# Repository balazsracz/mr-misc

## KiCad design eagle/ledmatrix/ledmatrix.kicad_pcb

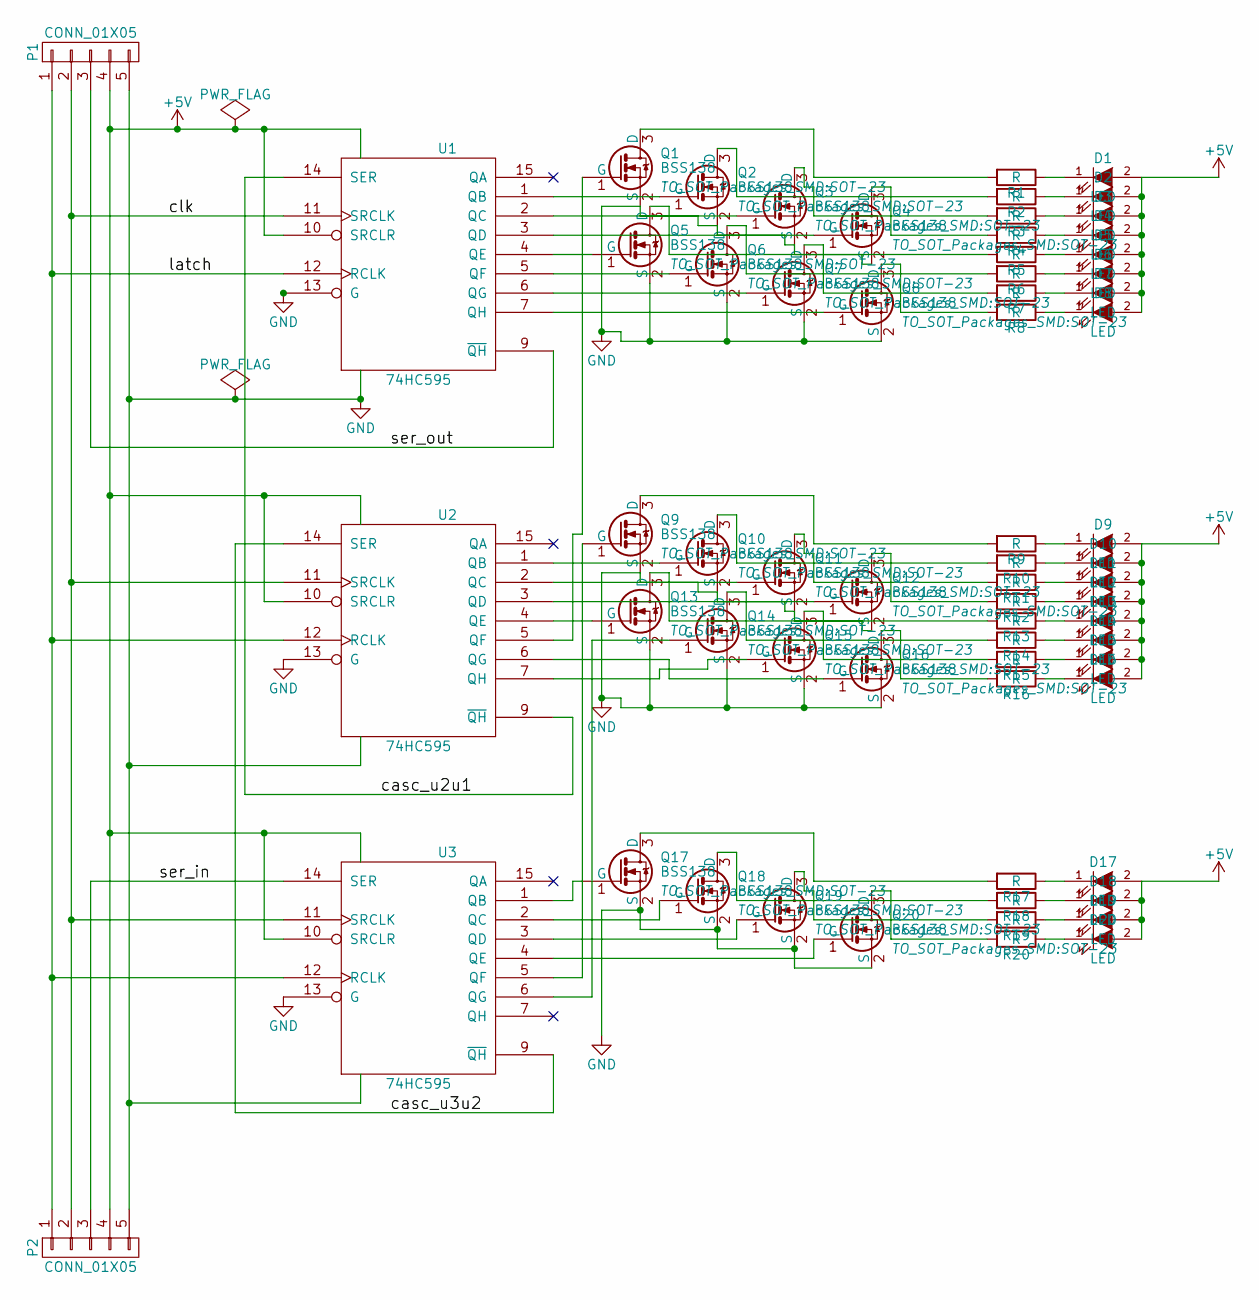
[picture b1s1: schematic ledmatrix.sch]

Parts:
D1, D2, D3, D4, D5, D6, D7, D8, D9, D10, D11, D12, D13, D14, D15, D16, D17, D18, D19, D20: LED; LED_PLCC_2835_Handsoldering
P1, P2: CONN_01X05; Pin_Header_Straight_1x05
Q1, Q2, Q3, Q4, Q5, Q6, Q7, Q8, Q9, Q10, Q11, Q12, Q13, Q14, Q15, Q16, Q17, Q18, Q19, Q20: BSS138; SOT-23
R1, R2, R3, R4, R5, R6, R7, R8, R9, R10, R11, R12, R13, R14, R15, R16, R17, R18, R19, R20: R; R_0805_HandSoldering
U1, U2, U3: 74HC595; SOIC-16_3.9x9.9mm_Pitch1.27mm

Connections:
+5V: D1.2 (A), D2.2 (A), D3.2 (A), D4.2 (A), D5.2 (A), D6.2 (A), D7.2 (A), D8.2 (A), D9.2 (A), D10.2 (A), D11.2 (A), D12.2 (A), D13.2 (A), D14.2 (A), D15.2 (A), D16.2 (A), D17.2 (A), D18.2 (A), D19.2 (A), D20.2 (A), P1.4, P2.4, U1.10 (SRCLR), U1.16 (VCC), U2.10 (SRCLR), U2.16 (VCC), U3.10 (SRCLR), U3.16 (VCC)
/casc_u2u1: U1.14 (SER), U2.9 (~QH)
/casc_u3u2: U2.14 (SER), U3.9 (~QH)
/clk: P1.2, P2.2, U1.11 (SRCLK), U2.11 (SRCLK), U3.11 (SRCLK)
/latch: P1.1, P2.1, U1.12 (RCLK), U2.12 (RCLK), U3.12 (RCLK)
/ser_in: P2.3, U3.14 (SER)
/ser_out: P1.3, U1.9 (~QH)
GND: P1.5, P2.5, Q1.2 (S), Q2.2 (S), Q3.2 (S), Q4.2 (S), Q5.2 (S), Q6.2 (S), Q7.2 (S), Q8.2 (S), Q9.2 (S), Q10.2 (S), Q11.2 (S), Q12.2 (S), Q13.2 (S), Q14.2 (S), Q15.2 (S), Q16.2 (S), Q17.2 (S), Q18.2 (S), Q19.2 (S), Q20.2 (S), U1.8 (GND), U1.13 (G), U2.8 (GND), U2.13 (G), U3.8 (GND), U3.13 (G)
unnamed: D1.1 (K), R1.1
unnamed: D2.1 (K), R2.1
unnamed: D3.1 (K), R3.1
unnamed: D4.1 (K), R4.1
unnamed: D5.1 (K), R5.1
unnamed: D6.1 (K), R6.1
unnamed: D7.1 (K), R7.1
unnamed: D8.1 (K), R8.1
unnamed: D9.1 (K), R9.1
unnamed: D10.1 (K), R10.1
unnamed: D11.1 (K), R11.1
unnamed: D12.1 (K), R12.1
unnamed: D13.1 (K), R13.1
unnamed: D14.1 (K), R14.1
unnamed: D15.1 (K), R15.1
unnamed: D16.1 (K), R16.1
unnamed: D17.1 (K), R17.1
unnamed: D18.1 (K), R18.1
unnamed: D19.1 (K), R19.1
unnamed: D20.1 (K), R20.1
unnamed: Q1.1 (G), U2.5 (QF)
unnamed: Q1.3 (D), R1.2
unnamed: Q2.1 (G), U1.1 (QB)
unnamed: Q2.3 (D), R2.2
unnamed: Q3.1 (G), U1.2 (QC)
unnamed: Q3.3 (D), R3.2
unnamed: Q4.1 (G), U1.3 (QD)
unnamed: Q4.3 (D), R4.2
unnamed: Q5.1 (G), U1.4 (QE)
unnamed: Q5.3 (D), R5.2
unnamed: Q6.1 (G), U1.5 (QF)
unnamed: Q6.3 (D), R6.2
unnamed: Q7.1 (G), U1.6 (QG)
unnamed: Q7.3 (D), R7.2
unnamed: Q8.1 (G), U1.7 (QH)
unnamed: Q8.3 (D), R8.2
unnamed: Q9.1 (G), U3.5 (QF)
unnamed: Q9.3 (D), R9.2
unnamed: Q10.1 (G), U2.1 (QB)
unnamed: Q10.3 (D), R10.2
unnamed: Q11.1 (G), U2.2 (QC)
unnamed: Q11.3 (D), R11.2
unnamed: Q12.1 (G), U2.3 (QD)
unnamed: Q12.3 (D), R12.2
unnamed: Q13.1 (G), U2.4 (QE)
unnamed: Q13.3 (D), R13.2
unnamed: Q14.1 (G), U3.6 (QG)
unnamed: Q14.3 (D), R14.2
unnamed: Q15.1 (G), U2.7 (QH)
unnamed: Q15.3 (D), R15.2
unnamed: Q16.1 (G), U2.6 (QG)
unnamed: Q16.3 (D), R16.2
unnamed: Q17.1 (G), U3.1 (QB)
unnamed: Q17.3 (D), R17.2
unnamed: Q18.1 (G), U3.2 (QC)
unnamed: Q18.3 (D), R18.2
unnamed: Q19.1 (G), U3.3 (QD)
unnamed: Q19.3 (D), R19.2
unnamed: Q20.1 (G), U3.4 (QE)
unnamed: Q20.3 (D), R20.2

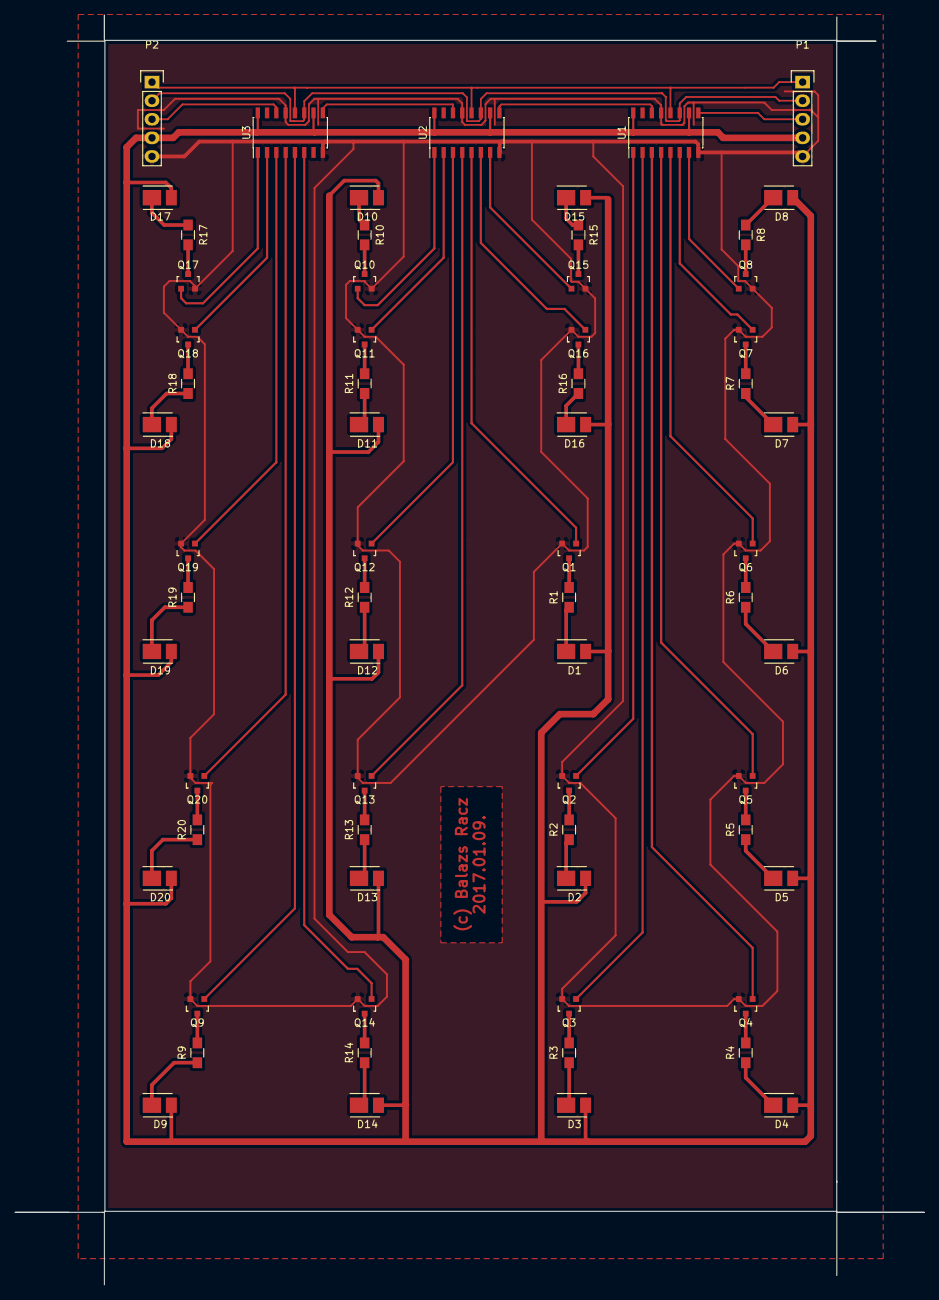
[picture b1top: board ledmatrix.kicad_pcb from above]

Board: 2 copper layers, 100.0 x 160.0 mm, 65 parts (0 on the bottom side), 68 nets.

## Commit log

2011-10-30 add initial list of stuff
2011-10-30 Baseline boxing command
2011-10-30 Add resistor definition command.
2011-10-30 check in CSV list
2011-11-05 finished labels tex code
2013-08-10 Workshop list generation code updates.
2013-08-10 Original source and binaries by D Nadler.
2013-08-10 Adds XC32 headers that are needed for the peripherial definitions.
2013-08-10 Changes needed to make the cpp demo compile.
2013-08-10 Removes generated files.
2013-08-10 Allows make dep to run without an exisitng depend file.
2013-08-12 Fixes compilation problems.
2013-08-12 Adpts nadler's code to PIC32MX795 on my board.
2013-08-12 Adds bootloader code with changes needed to make it compile.
2013-08-12 Adds missing file for the 795.
2013-08-12 Switches bootloader to 80MHz. Updates USB bootloader to not require interrupt flag table, which is huge. Renamed to bootloader.{elf,hex} Removes the CS3 startup code which is huge. Supplies custom st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
2013-08-12 Moves the bootloader into the bootloader area. Updates the app start pointers.
2013-08-12 Working bootloader.
2014-06-06 Updates the fuses to match the duinomite mega better. Enables block switching.
2014-06-06 Fixes compilation errors.
2014-06-06 changes the include guard to avoid clashes with openmrn.
2014-06-06 updates bootloader fuses.
2015-03-16 Adds base versions of the mixxx controller scripts.
2015-03-16 Removes the headphone volume control. Adds script bindings to the fwd and back buttons.
2015-03-16 starts adding onfwd onback javascript functions.
2015-03-16 Adds handling for onFwd.
2015-03-16 removes key off bindings from the onfwd onback commands.
2015-03-16 Fixes bug in onFwd that caused it to trigger on key up as well.
2015-03-16 Adds onBack implementation.
2015-03-16 Fixes broken script-binding.
2015-03-16 Adds a couple of buttons as soft buttons.
2015-03-16 Implements beats translation on soft button 4.
2015-04-19 moves an onsoftbutton defn.
2015-04-19 Adds the ability to catch wheel turn (not jog) operations in javascript.
2015-05-14 adds scratching support when the deck is not playing.
2015-10-25 'We use math' tex logo.
2015-10-25 adds gitignore for parts.
2015-10-25 adds gitignore.
2015-10-25 trainlib historical commit 2014-10-31
2015-10-25 trainlib historical commit 2014-10-31-2
2015-10-25 trainlib historical commit 2014-10-31-3
2015-10-25 trainlib historical commit 2014-10-31-4
2015-10-25 trainlib historical commit 2014-11-01-1
2015-10-25 trainlib historical commit 2014-11-01-2
2015-10-25 trainlib historical commit 2014-11-01-3
2015-10-25 trainlib historical commit 2015-07-25-1
2015-10-25 trainlib historical commit 2015-07-25-3
2015-10-25 trainlib historical commit 2015-07-27-1
2015-10-25 trainlib historical commit 2015-07-27-2
2015-10-25 trainlib historical commit 2015-08-31-1
2015-10-25 trainlib historical commit 2015-08-31-2
2015-10-25 trainlib historical commit 2015-08-31-3
2015-10-25 trainlib historical commit 2015-08-31-4
2015-10-25 trainlib current
2015-10-26 adds/updates rj45 jacks. adds a 0R bridge.
2015-11-27 smd reflow oven testing pattern
2015-11-27 Adds basic makefile and blink binary
2015-11-27 Adds qr code files.
2015-11-27 checks in bootloader source
2015-11-29 Adds eagle library file used by the project.
2015-12-01 adds a test of the led hardware during the bootup of the bootloader.
2015-12-01 cleanup library
2015-12-02 original bootloader offset
2015-12-02 updates codeoffset.
2015-12-02 removes outpout file
2015-12-02 ignores hex files
2015-12-02 Adds usb driver source to firmware library.
2015-12-02 adds usb options to makefile
2015-12-02 rendered schematics
2015-12-02 older version
2015-12-02 adds gitignore
2015-12-02 updates yellow on rgb
2015-12-02 cleanup blink code
2015-12-02 Adds all the steps for the firmware training.
2015-12-03 Adds binaries for flashing usb-hid bootloaders.
2015-12-03 adds mac specific makefile
2015-12-03 create bin dir
2015-12-03 actually use the flash variable
2015-12-08 Adds production firmware.
2016-05-15 Adds a test application to debug the USB-CDC device driver.
2016-05-15 Adds new device DMG6601LVT.
2016-05-15 Adds esp12-huzzah breakout board.
2016-05-15 Adds pololu voltage regulator.
2016-05-15 Finishes deadrail schematics (en gross).
2016-05-17 Adds esp12-huzzah board definition.
2016-05-17 autorouter definitions for etching.
2016-05-17 Adds all intermediate and the final schematic and board layout for the huzzah baseboard for esp-12 train decoder.
2016-06-04 Adds a bunch of parts to the lib that are used in the deadrail controller.
2016-06-04 Checks in the adafruit eagle library downloaded from their webpage.
2016-06-04 Adds first versions of the schematics for the native deadrail decoder implementation.
2016-06-05 Adds through-hole version of esp-12. Adds rectifier bridge in sot format. Adds analog mux. Adds pinheaders for hand soldering.
2016-06-05 Fixes unloadable schematics
2016-06-05 Adds all intermediate and the final rendering of the design.
2016-06-06 Adds the esp-12 in the original form from the adafruit library and makes the rounding outline smaller.
2016-06-06 Adds variants with polygon and a bunch of ground vias.
2016-06-06 Adds gerber output.
2016-06-23 submitted file.
2016-07-26 Check in compiled version of the bootloader (with full optimization so it fits in 4K).
2016-07-26 Adds dependency list.
2016-07-27 Adds a firmware that can be used to test the solder job.
2016-07-28 Stop sending zeros to the hostfrom the usb-serial device. It makes various host program confused.
2016-07-28 Change the USB-reported product name so that we can recognize these devices from software.
2016-07-28 Adds trim dependency.
2016-07-28 Adds data logger application that writes to google sheets.
2016-07-28 Actually call init().
2016-09-07 update DRU
2016-09-07 Check in ledmatrix rules.
2016-09-09 continue work on the ledmatrix schematic and board.
2016-09-09 Adds outlines.
2016-09-09 adds brokenusb test
2016-09-09 layout components.
2016-09-09 more routing -- latch, clock proposal 1
2016-09-09 all routed
2016-09-09 adds ground fill.
2016-09-09 regenrates fill. Adds rendered board.
2017-05-06 Adds drawing of the laser-cutted bridge.
2017-05-06 Adds new versions of the bridge design.
2017-05-07 New design with small fixes of the bridge
2018-04-01 Checks in missing files.
2018-04-01 Adds nucleo 64 library element.
2018-04-01 Start of the io board based on the nucleo base.
2018-04-05 Adds AP1509 and a through hole inductor.
2018-04-05 Adds version of the nucleo board with inputs, the switching PS and part of the tortoise driver.
2018-04-09 Ignores backup files by eagle.
2018-04-09 Adds seed DRU file
2018-04-09 Adds round solder jumpers; solder jumpers that are default-closed Updates DIL-8 package to have standard footprint Adds package outline to 0.1" terminal block Adds DIL18 footprint with small solder t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
2018-04-09 More work on the nucleo io board.
2018-04-14 more versions of the io board.
2018-04-15 Adds better (polygon based) round solder bridge. Moves CAN transceiver to create a small-hole DIL8 package version.
2018-04-15 Finishes routing the io board. Adds four more servo outputs.
2018-04-19 Latest versions.
2018-04-22 updates some components.
2018-04-22 Adds more iterations of the io board.
2018-05-06 Moves layer designations for the power notice component.
2018-05-06 Adds a package for denoting revision.
2018-05-06 Removes the ground polygon inside the cutaway wire of the SJ-C.
2018-05-06 Rev A final version.
2018-05-06 Moves a couple of parts to the custom library to allow renaming prefix to U instead of IC.
2018-05-06 Progress towards rev B.
2018-05-06 Adds missing prefixes.
2018-05-08 Modifies the DC jack part to not have overlapping mills and drill.
2018-05-08 New revisions to fix comments from the review process.
2018-05-12 More versions of the board design.
2018-05-12 DCjack: removes overlapping wires on the via layer that cause conflict.
2018-05-21 Adds DPDT switch adds micro-USB receptacle adds larger pinheaders adds a CC3220SF launchpad HAT footprint.
2018-05-21 Adds programming adapter board.
2018-05-21 adds individual gerber files of the jtag adapter.
2018-05-21 Adds RJ45 adaptor board.
2018-05-23 Adds deduplicator python code.
2018-05-23 Adds copyright notice
2018-05-26 Adds first covering algorithm.
2018-05-26 Adds code to apply rules specifically to filter files with lots of duplicates.
2018-06-11 Fixes launchpad jtag-HAT footprint. Fixes bounding box on siklscreen for the 0.05" jtag header.
2018-06-11 Fixes prototype problems.
2018-07-07 Imports loconet library from arduino library manager.
2018-07-07 Adds empty shell for openmrn library.
2018-07-08 moves library to src directory for 1.5. format.
2018-07-08 switches library to .a linkage.
2018-07-08 Adds symlinks to the openmrn implementation code.
2018-07-08 Adds support for Serial ports via gridconnect hub.
2018-07-24 Adds code for CAN bridge.
2018-07-24 Adds more symlinks for arduino codebase.
2018-07-24 Adds example sketch with openmrn.
2018-07-24 Adds another test copy of the arduino library.
2018-09-09 Fix inlining problem with new GCC compilation.
2018-09-10 recompiles bootloader.
2019-01-13 Updates resistor values.
2019-01-13 Updates frame grid.
